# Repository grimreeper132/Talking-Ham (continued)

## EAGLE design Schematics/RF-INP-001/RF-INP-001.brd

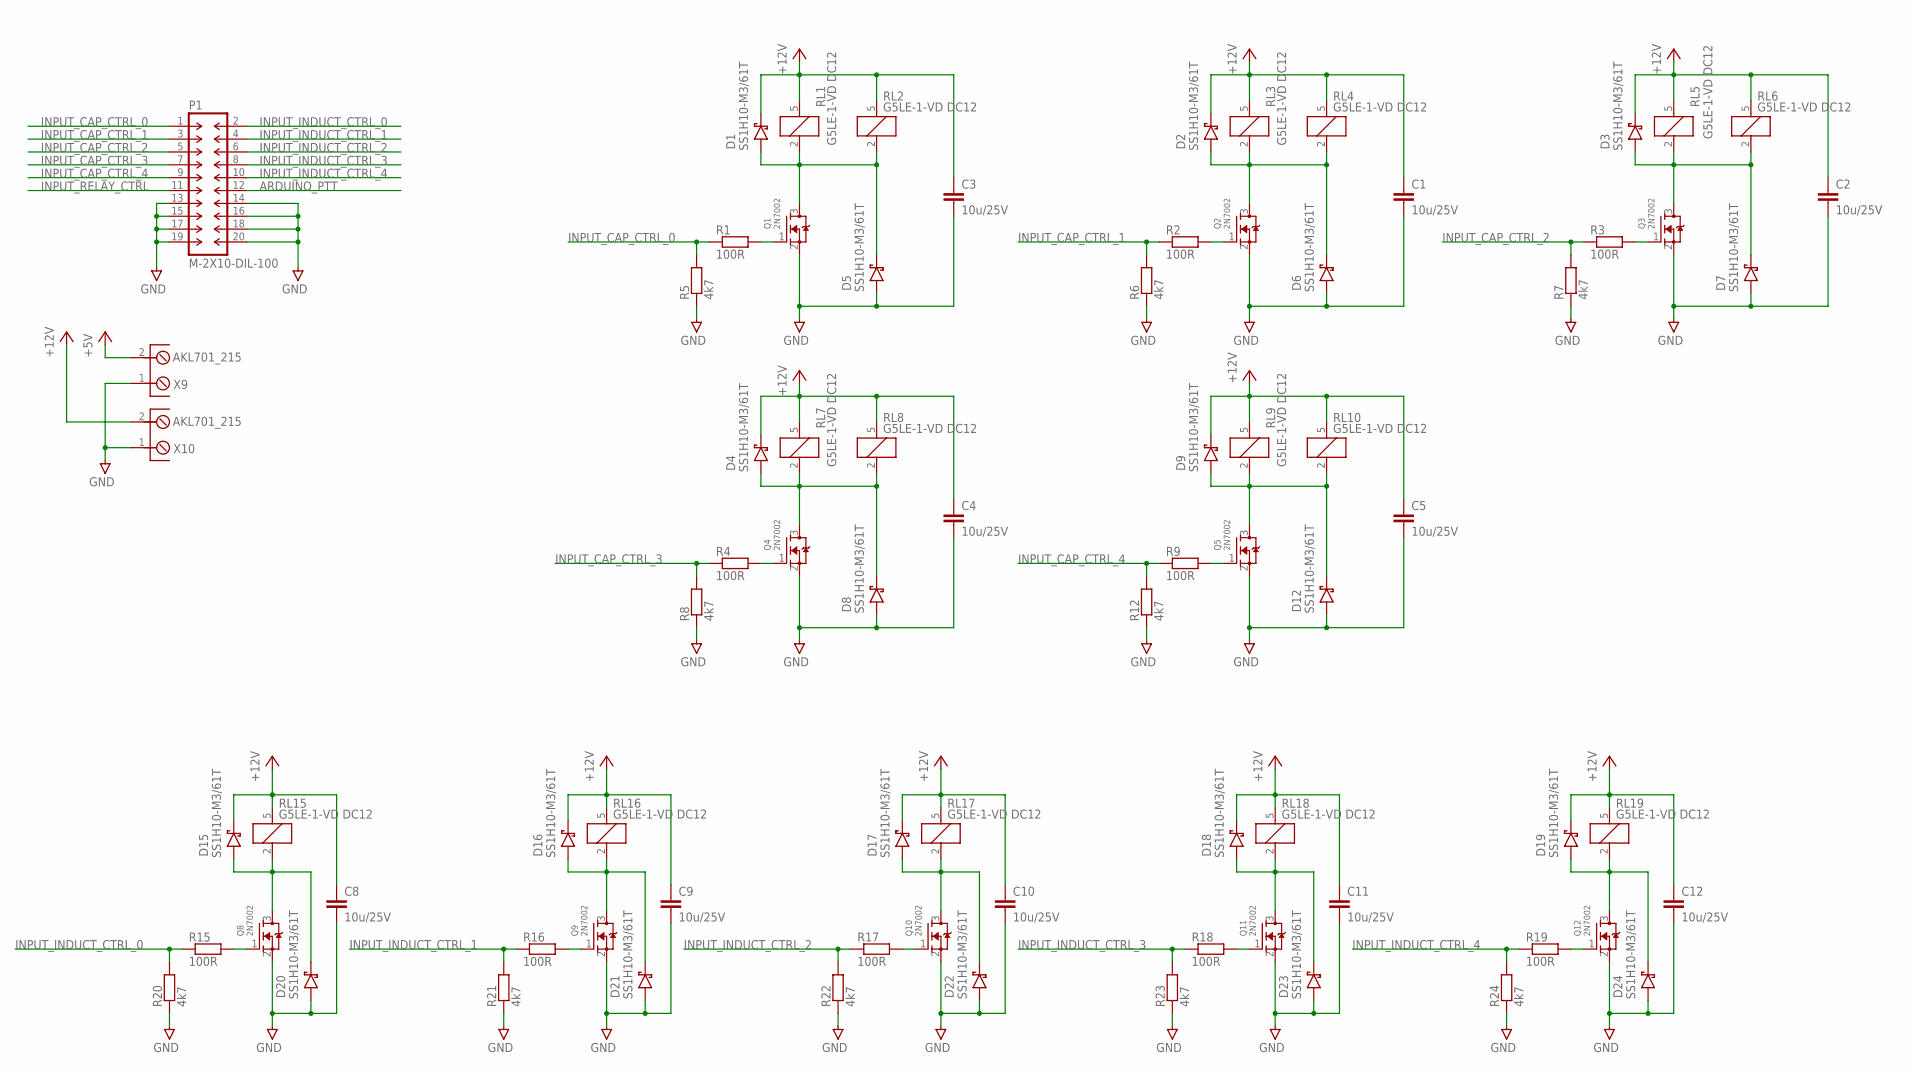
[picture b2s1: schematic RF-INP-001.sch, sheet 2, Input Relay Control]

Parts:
C1, C2, C3, C4, C5, C8, C9, C10, C11, C12: 10u/25V; C0805
D1, D2, D3, D4, D5, D6, D7, D8, D9, D12, D15, D16, D17, D18, D19, D20, D21, D22, D23, D24: SS1H10-M3/61T; SMA/DO-214AC
P1: M-2X10-DIL-100; DIL-100-2X10
Q1, Q2, Q3, Q4, Q5, Q8, Q9, Q10, Q11, Q12: 2N7002; SOT23
R1, R2, R3, R4, R9, R15, R16, R17, R18, R19: 100R; R0603
R5, R6, R7, R8, R12, R20, R21, R22, R23, R24: 4k7; R0603
RL1, RL2, RL3, RL4, RL5, RL6, RL7, RL8, RL9, RL10, RL15, RL16, RL17, RL18, RL19: G5LE-1-VD DC12; SPDT
X9, X10: AKL701_215; AKL701_2_15

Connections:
+5V: X9.2; also elsewhere on the board
+12V: C1.1, C2.1, C3.1, C4.1, C5.1, C8.1, C9.1, C10.1, C11.1, C12.1, D1.C (CATHODE), D2.C (CATHODE), D3.C (CATHODE), D4.C (CATHODE), D9.C (CATHODE), D15.C (CATHODE), D16.C (CATHODE), D17.C (CATHODE), D18.C (CATHODE), D19.C (CATHODE), RL1.5, RL2.5, RL3.5, RL4.5, RL5.5, RL6.5, RL7.5, RL8.5, RL9.5, RL10.5, RL15.5, RL16.5, RL17.5, RL18.5, RL19.5, X10.2; also elsewhere on the board
ARDUINO_PTT: P1.12; also elsewhere on the board
GND: C1.2, C2.2, C3.2, C4.2, C5.2, C8.2, C9.2, C10.2, C11.2, C12.2, D5.A (ANODE), D6.A (ANODE), D7.A (ANODE), D8.A (ANODE), D12.A (ANODE), D20.A (ANODE), D21.A (ANODE), D22.A (ANODE), D23.A (ANODE), D24.A (ANODE), P1.13, P1.14, P1.15, P1.16, P1.17, P1.18, P1.19, P1.20, Q1.2 (S), Q2.2 (S), Q3.2 (S), Q4.2 (S), Q5.2 (S), Q8.2 (S), Q9.2 (S), Q10.2 (S), Q11.2 (S), Q12.2 (S), R5.1, R6.1, R7.1, R8.1, R12.1, R20.1, R21.1, R22.1, R23.1, R24.1, X9.1, X10.1; also elsewhere on the board
INPUT_CAP_CTRL_0: P1.1, R1.1, R5.2
INPUT_CAP_CTRL_1: P1.3, R2.1, R6.2
INPUT_CAP_CTRL_2: P1.5, R3.1, R7.2
INPUT_CAP_CTRL_3: P1.7, R4.1, R8.2
INPUT_CAP_CTRL_4: P1.9, R9.1, R12.2
INPUT_INDUCT_CTRL_0: P1.2, R15.1, R20.2
INPUT_INDUCT_CTRL_1: P1.4, R16.1, R21.2
INPUT_INDUCT_CTRL_2: P1.6, R17.1, R22.2
INPUT_INDUCT_CTRL_3: P1.8, R18.1, R23.2
INPUT_INDUCT_CTRL_4: P1.10, R19.1, R24.2
INPUT_RELAY_CTRL: P1.11; also elsewhere on the board
unnamed: D16.A (ANODE), D21.C (CATHODE), Q9.3 (D), RL16.2
unnamed: Q9.1 (G), R16.2
unnamed: D17.A (ANODE), D22.C (CATHODE), Q10.3 (D), RL17.2
unnamed: Q10.1 (G), R17.2
unnamed: D18.A (ANODE), D23.C (CATHODE), Q11.3 (D), RL18.2
unnamed: Q11.1 (G), R18.2
unnamed: D19.A (ANODE), D24.C (CATHODE), Q12.3 (D), RL19.2
unnamed: Q12.1 (G), R19.2
unnamed: D1.A (ANODE), D5.C (CATHODE), Q1.3 (D), RL1.2, RL2.2
unnamed: Q1.1 (G), R1.2
unnamed: D2.A (ANODE), D6.C (CATHODE), Q2.3 (D), RL3.2, RL4.2
unnamed: Q2.1 (G), R2.2
unnamed: D4.A (ANODE), D8.C (CATHODE), Q4.3 (D), RL7.2, RL8.2
unnamed: Q4.1 (G), R4.2
unnamed: D9.A (ANODE), D12.C (CATHODE), Q5.3 (D), RL9.2, RL10.2
unnamed: Q5.1 (G), R9.2
unnamed: D3.A (ANODE), D7.C (CATHODE), Q3.3 (D), RL5.2, RL6.2
unnamed: Q3.1 (G), R3.2
unnamed: D15.A (ANODE), D20.C (CATHODE), Q8.3 (D), RL15.2
unnamed: Q8.1 (G), R15.2

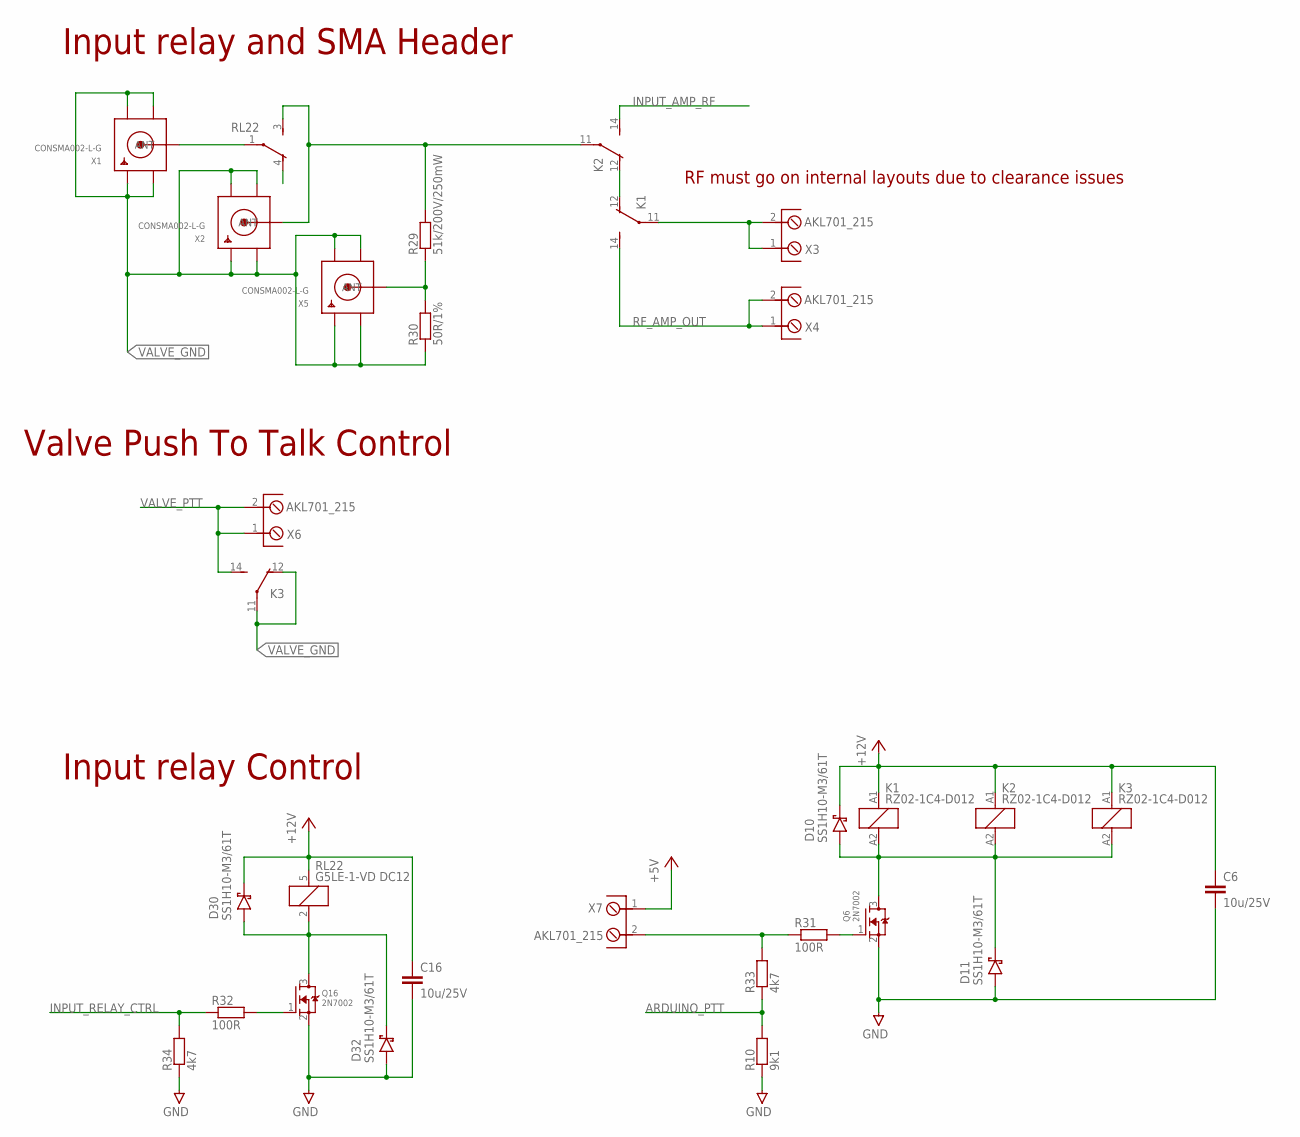
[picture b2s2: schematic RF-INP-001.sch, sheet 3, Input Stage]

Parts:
C6, C16: 10u/25V; C0805
D10, D11, D30, D32: SS1H10-M3/61T; SMA/DO-214AC
K1, K2, K3: RZ02-1C4-D012; 12A-5MM
Q6, Q16: 2N7002; SOT23
R10: 9k1; R0603
R29: 51k/200V/250mW; R2512
R30: 50R/1%; R0603
R31, R32: 100R; R0603
R33, R34: 4k7; R0603
RL22: G5LE-1-VD DC12; SPDT
X1, X2, X5: CONSMA002-L-G; SMA90_DIP
X3, X4, X6, X7: AKL701_215; AKL701_2_15

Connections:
+5V: X7.1; also elsewhere on the board
+12V: C6.1, C16.1, D10.C (CATHODE), D30.C (CATHODE), K1.A1 (1), K2.A1 (1), K3.A1 (1), RL22.5; also elsewhere on the board
ARDUINO_PTT: R10.2, R33.1; also elsewhere on the board
GND: C6.2, C16.2, D11.A (ANODE), D32.A (ANODE), Q6.2 (S), Q16.2 (S), R10.1, R34.1; also elsewhere on the board
INPUT_AMP_RF: K2.14 (NO); also elsewhere on the board
INPUT_RELAY_CTRL: R32.1, R34.2; also elsewhere on the board
unnamed: D10.A (ANODE), D11.C (CATHODE), K1.A2 (2), K2.A2 (2), K3.A2 (2), Q6.3 (D)
unnamed: K1.12 (NC), K2.12 (NC)
unnamed: K1.11 (COM), X3.1, X3.2
unnamed: Q6.1 (G), R31.2
unnamed: D30.A (ANODE), D32.C (CATHODE), Q16.3 (D), RL22.2
unnamed: Q16.1 (G), R32.2
unnamed: R29.1, R30.2, X5.ANTENNA (ANT)
unnamed: RL22.1, X1.ANTENNA (ANT)
unnamed: R31.1, R33.2, X7.2
unnamed: K2.11 (COM), R29.2, RL22.3, X2.ANTENNA (ANT)
RF_AMP_OUT: K1.14 (NO), X4.1, X4.2
VALVE_GND: K3.11 (COM), K3.12 (NC), R30.1, X1.GND1, X1.GND2, X1.GND3, X1.GND4, X2.GND1, X2.GND2, X2.GND3, X2.GND4, X5.GND1, X5.GND2, X5.GND3, X5.GND4; also elsewhere on the board
VALVE_PTT: K3.14 (NO), X6.1, X6.2

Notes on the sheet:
Input relay and SMA Header
Input relay Control
Valve Push To Talk Control
RF must go on internal layouts due to clearance issues

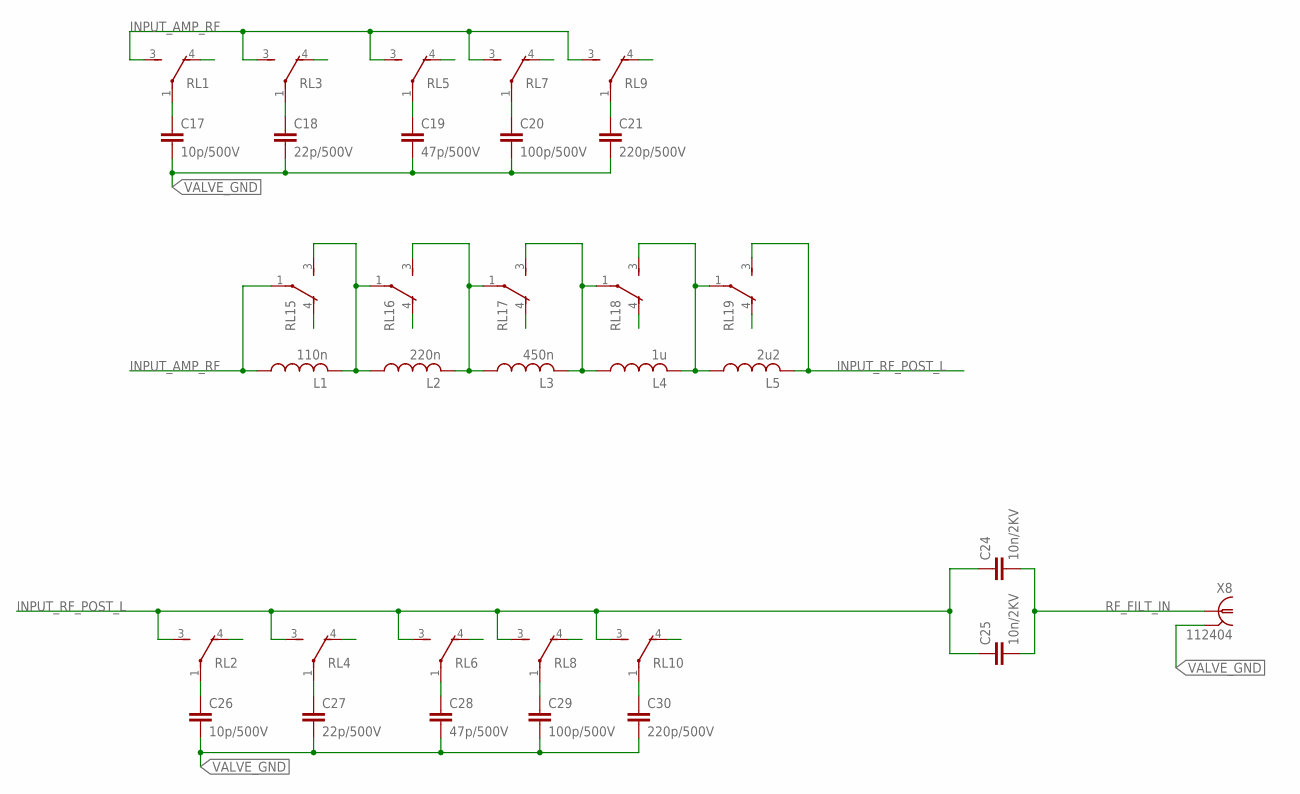
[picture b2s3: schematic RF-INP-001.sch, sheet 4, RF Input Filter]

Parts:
C17, C26: 10p/500V; C1812
C18, C27: 22p/500V; C1812
C19, C28: 47p/500V; C1812
C20, C29: 100p/500V; C1812
C21, C30: 220p/500V; C1812
C24, C25: 10n/2KV; C1812
L1: 110n; T80-6
L2: 220n; T80-6
L3: 450n; T80-6
L4: 1u; T80-6
L5: 2u2; T80-6
RL1, RL2, RL3, RL4, RL5, RL6, RL7, RL8, RL9, RL10, RL15, RL16, RL17, RL18, RL19: G5LE-1-VD DC12; SPDT
X8: 112404

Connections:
INPUT_AMP_RF: L1.1, RL1.3, RL3.3, RL5.3, RL7.3, RL9.3, RL15.1; also elsewhere on the board
INPUT_RF_POST_L: C24.1, C25.1, L5.2, RL2.3, RL4.3, RL6.3, RL8.3, RL10.3, RL19.3
unnamed: C17.1, RL1.1
unnamed: C26.1, RL2.1
unnamed: C27.1, RL4.1
unnamed: C28.1, RL6.1
unnamed: C29.1, RL8.1
unnamed: C30.1, RL10.1
unnamed: C18.1, RL3.1
unnamed: C19.1, RL5.1
unnamed: C21.1, RL9.1
unnamed: C20.1, RL7.1
unnamed: L4.2, L5.1, RL18.3, RL19.1
unnamed: L3.2, L4.1, RL17.3, RL18.1
unnamed: L2.2, L3.1, RL16.3, RL17.1
unnamed: L1.2, L2.1, RL15.3, RL16.1
RF_FILT_IN: C24.2, C25.2, X8.1
VALVE_GND: C17.2, C18.2, C19.2, C20.2, C21.2, C26.2, C27.2, C28.2, C29.2, C30.2, X8.2, X8.3 (2), X8.4 (2), X8.5 (2); also elsewhere on the board

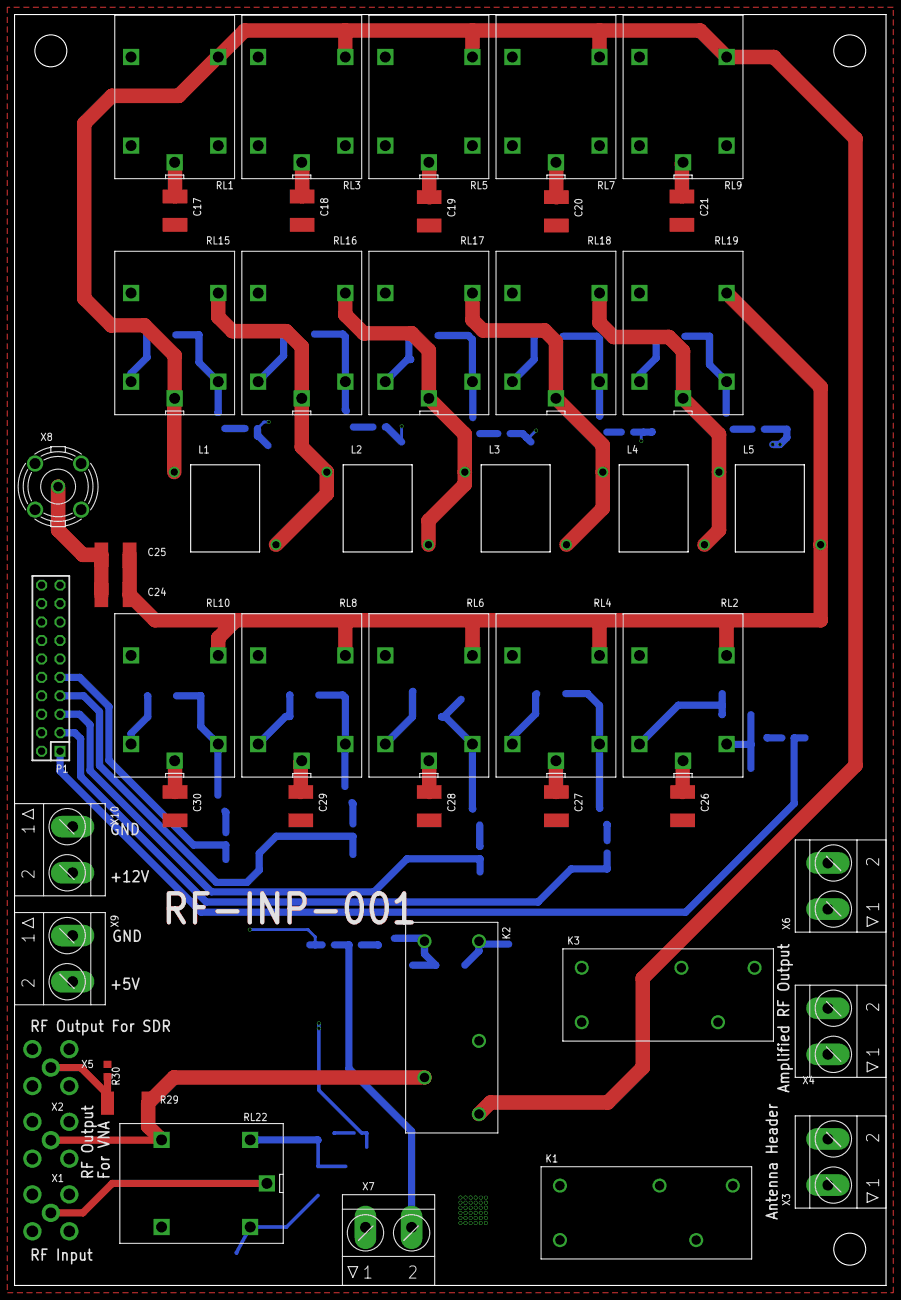
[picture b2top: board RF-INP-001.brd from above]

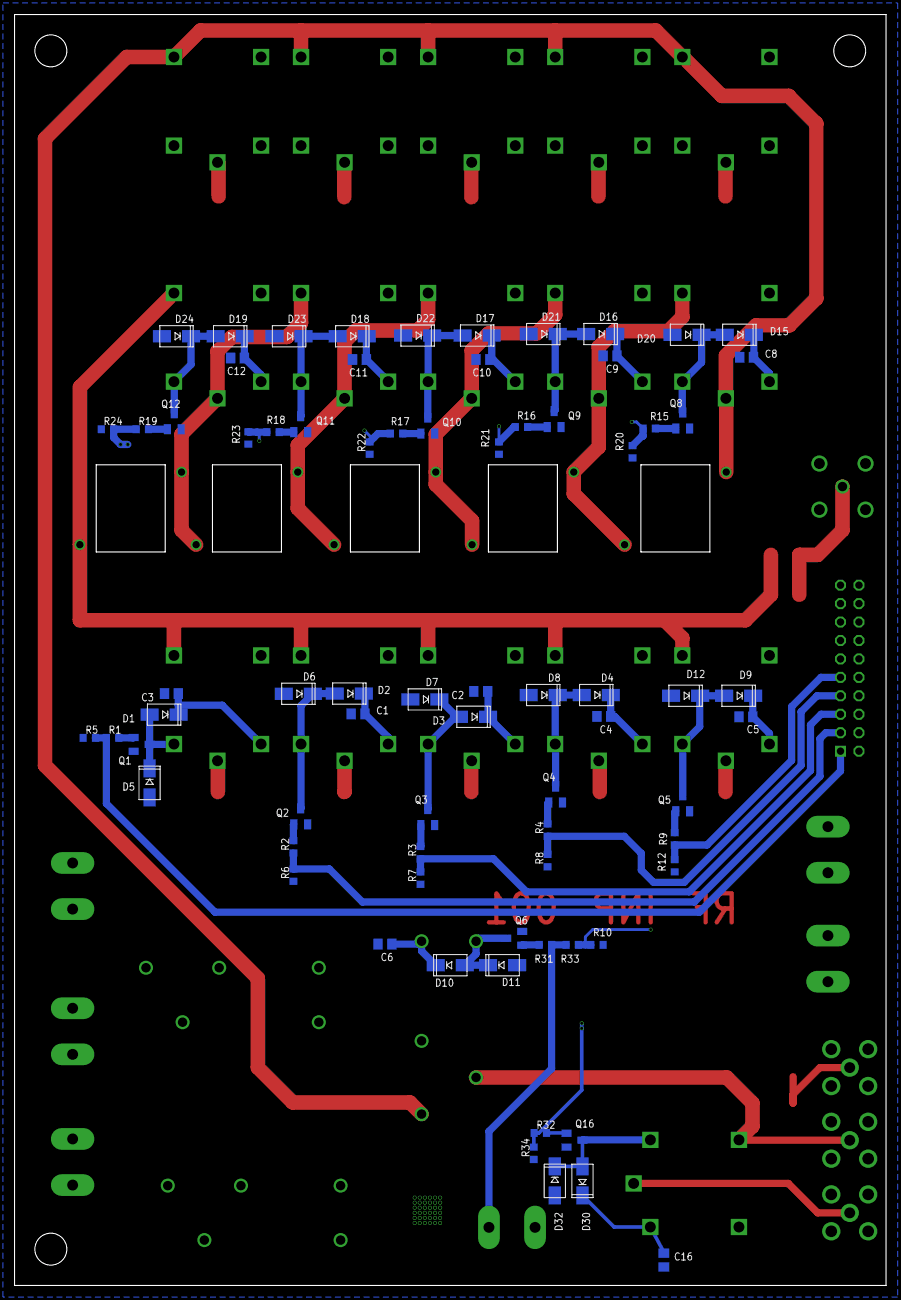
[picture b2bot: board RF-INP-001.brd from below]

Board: 4 copper layers, 120.0 x 175.0 mm, 122 parts (73 on the bottom side), 65 nets.

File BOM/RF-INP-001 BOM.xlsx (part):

|  |  | Board ID |  |  | Engineer |  |  | Project |  |  | Job NO.
 |  |  | Revision | 1 |  | Approval |  |  | Customer |  |  | Boards Required | 1
 | (don't touch)
 | Component Number | Type Colour | Schematic Ref | Quantity | Spare Parts | Description | Footprint | Value | Tolerance | Manufacturer | Manufacturer Part Number | Preferred Supplier | Order-code | Alternate Supplier | Alt Order-Code | Unit/Reel Price | Packaging | Reel QTY | Stock | Price per board | Total Price (all boards) | Order Quantity | Order Price
 | 0 | 1 | C1, C2, C3, C4, C5, C6, C8, C9, C10, C11, C12, C16 | 12 |  | X5R Ceramic Capacitor | C0805 | 10u/25V |  | Samsung Electro-Mechanics | CL21A106KAYNNNE | Mouser | 187-CL21A106KAYNNNE |  |  | 0.13700000000000001 | Cut Tape | 1000 |  | 1.6440000000000001 | 1.6440000000000001 | 12 | 1.6440000000000001
 | 1 | 2 | R1, R2, R3, R4, R9, R15, R16, R17, R18, R19, R31, R32 | 12 |  | Thick Film Resistor | R0603 | 100R | 0.01 | Vishay/Dale | CRCW0603100RFKEAC | Mouser | 71-CRCW0603100RFKEAC |  |  | 7.6999999999999999E-2 | Cut Tape | 1000 |  | 0.92399999999999993 | 0.92399999999999993 | 12 | 0.92399999999999993
 | 2 | 2 | R29 | 1 |  | Thick Film Resistor | R2512 | 51k/200V/250mW | 0.05 | Yageo | RC2512JK-0751KL | Mouser | 603-RC2512JK-0751KL |  |  | 0.27500000000000002 | Cut Tape | 1000 |  | 0.27500000000000002 | 0.27500000000000002 | 1 | 0.27500000000000002
 | 3 | 2 | R30 | 1 |  | Thick Film Resistor | R0603 | 50R | 0.01 | Vishay / Dale | CRCW060350R0FKTA | Mouser | 71-CRCW0603-50 |  |  | 0.17599999999999999 | Cut Tape | 1000 |  | 0.17599999999999999 | 0.17599999999999999 | 1 | 0.17599999999999999
 | 4 | 2 | R5, R6, R7, R8, R10, R12, R20, R21, R22, R23, R24, R34 | 12 |  | Thick Film Resistor | R0603 | 4k7 | 0.05 | Vishay / Dale | CRCW06034K70JNEAC | Mouser | 71-CRCW06034K70JNEAC |  |  | 7.6999999999999999E-2 | Cut Tape | 1000 |  | 0.92399999999999993 | 0.92399999999999993 | 12 | 0.92399999999999993
 | 5 | 2 | R33 | 1 |  | Thick Film Resistor | R0603 | 9k1 | 0.05 | ROHM Semiconductor | SDR03EZPJ912 | Mouser | 755-SDR03EZPJ912 |  |  | 7.6999999999999999E-2 | Cut Tape | 1000 |  | 7.6999999999999999E-2 | 7.6999999999999999E-2 | 1 | 7.6999999999999999E-2
 | 6 | 3 | L1 | 1 |  | RF Inductor Toroid Core | T80-6 | 5 turns 20 AWG |  | Micrometals | T60-6 | Pace Components | link |  |  | 0.88 | Cut Tape | 1000 |  | 0.88 | 0.88 | 1 | 0.88
 | 7 | 3 | L2 | 1 |  | RF Inductor Toroid Core | T80-6 | 7 turns 20 AWG |  | Micrometals | T60-6 | Pace Components | link |  |  | 0.88 | Cut Tape | 1000 |  | 0.88 | 0.88 | 1 | 0.88
 | 8 | 3 | L3 | 1 |  | RF Inductor Toroid Core | T80-6 | 10 turns 20 AWG |  | Micrometals | T60-6 | Pace Components | link |  |  | 0.88 | Cut Tape | 1000 |  | 0.88 | 0.88 | 1 | 0.88
 | 9 | 3 | L4 | 1 |  | RF Inductor Toroid Core | T80-6 | 15 turns 20 AWG |  | Micrometals | T60-6 | Pace Components | link |  |  | 0.88 | Cut Tape | 1000 |  | 0.88 | 0.88 | 1 | 0.88
 | 10 | 3 | L5 | 1 |  | RF Inductor Toroid Core | T80-6 | 22 turns 20 AWG |  | Micrometals | T60-6 | Pace Components | link |  |  | 0.88 | Cut Tape | 1000 |  | 0.88 | 0.88 | 1 | 0.88
 | 11 | 4 | D1, D2, D3, D4, D5, D6, D7, D8, D9, D10, D11, D12, D15, D16, D17, D18, D19, D20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 | 24 |  | Schottky Diode | SMA | 0.62V 1A |  | Vishay General Semiconductor | SS1H10-M3/61T | Mouser | 78-SS1H10-M361T |  |  | 0.28199999999999997 | Cut Tape | 1000 |  | 6.7679999999999989 | 6.7679999999999989 | 24 | 6.7679999999999989
 | 12 | 6 | Q1, Q2, Q3, Q4, Q5, Q6, Q8, Q9, Q10, Q11, Q12, Q16 | 12 |  | N-Channel MOSFET | SOT23 |  |  | Nexperia | 2N7002NXAKR | Mouser | 771-2N7002NXAKR |  |  | 7.6999999999999999E-2 | Cut Tape | 1000 |  | 0.92399999999999993 | 0.92399999999999993 | 12 | 0.92399999999999993
 | 13 | 7 | K1, K2, K3 | 3 |  | General Purpose Relay | Custom |  |  | TE Connectivity / P&B | 3-1415899-5 | Mouser | 655-3-1415899-5 |  |  | 1.5 | Cut Tape | 1000 |  | 4.5 | 4.5 | 3 | 4.5
 | 14 | 7 | P1 | 1 |  | 20 pin Headeer | 2.54mm 2 by 10 pos | 20 pins |  | Amphenol FCI | 10129381-920001BLF | Mouser | 649-1012938192001BLF |  |  | 0.32800000000000001 | Cut Tape | 1000 |  | 0.32800000000000001 | 0.32800000000000001 | 1 | 0.32800000000000001
 | 15 | 7 | RL1, RL2, RL3, RL4, RL5, RL6, RL7, RL8, RL9, RL10, RL15, RL16, RL17, RL18, RL19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 | 16 |  | General Purpose Relay | G5LE | SPDT |  | Omron Electronics | G5LE-1-VD DC12 | Mouser | 653-G5LE-1-VDDC12 |  |  | 1.07 | Cut Tape | 1000 |  | 17.12 | 17.12 | 16 | 17.12
 | 16 | 8 | X1, X2, X5 | 3 |  | SMA Connector | Through hole SMA |  |  | Linx Technologies | CONSMA002-L-G | Mouser | 712-CONSMA002-L-G | Digi-Key | CONSMA002-L-G-ND | 3.11 | Cut Tape | 1000 |  | 9.33 | 9.33 | 3 | 9.33
 | 17 | 8 | X3, X4, X6, X7, X9, X10 | 6 |  | Terminal Block | 6.35mm 2 pos | 2 pos |  | Phoenix Contact | 1714955 | Mouser | 651-1714955 | Digi-Key | 277-1269-ND | 0.96299999999999997 | Cut Tape | 1000 |  | 5.7779999999999996 | 5.7779999999999996 | 6 | 5.7779999999999996
 | 18 | 8 | X8 | 1 |  | BNC RF Connector | TH BNC |  |  | Amphenol RF | 112404 | Mouser | 523-112404 |  |  | 2.1800000000000002 | Cut Tape | 1000 |  | 2.1800000000000002 | 2.1800000000000002 | 1 | 2.1800000000000002
 | 19 |  |  |  |  |  |  |  |  |  |  |  |  |  |  |  | Cut Tape | 1000 |  | 0 | 0 | 0 | 0
 | 20 |  |  |  |  |  |  |  |  |  |  |  |  |  |  |  | Cut Tape | 1000 |  | 0 | 0 | 0 | 0
 | 21 |  |  |  |  |  |  |  |  |  |  |  |  |  |  |  | Cut Tape | 1000 |  | 0 | 0 | 0 | 0
 | 22 |  |  |  |  |  |  |  |  |  |  |  |  |  |  |  | Cut Tape | 1000 |  | 0 | 0 | 0 | 0
 | 23 |  |  |  |  |  |  |  |  |  |  |  |  |  |  |  | Cut Tape | 1000 |  | 0 | 0 | 0 | 0
 | 24 |  |  |  |  |  |  |  |  |  |  |  |  |  |  |  | Cut Tape | 1000 |  | 0 | 0 | 0 | 0
 | 25 |  |  |  |  |  |  |  |  |  |  |  |  |  |  |  | Cut Tape | 1000 |  | 0 | 0 | 0 | 0
 | 26 |  |  |  |  |  |  |  |  |  |  |  |  |  |  |  | Cut Tape | 1000 |  | 0 | 0 | 0 | 0
 | 27 |  |  |  |  |  |  |  |  |  |  |  |  |  |  |  | Cut Tape | 1000 |  | 0 | 0 | 0 | 0
 | 28 |  |  |  |  |  |  |  |  |  |  |  |  |  |  |  | Cut Tape | 1000 |  | 0 | 0 | 0 | 0
 | 29 |  |  |  |  |  |  |  |  |  |  |  |  |  |  |  | Cut Tape | 1000 |  | 0 | 0 | 0 | 0
 | 30 |  |  |  |  |  |  |  |  |  |  |  |  |  |  |  | Cut Tape | 1000 |  | 0 | 0 | 0 | 0
 | 31 |  |  |  |  |  |  |  |  |  |  |  |  |  |  |  | Cut Tape | 1000 |  | 0 | 0 | 0 | 0
 | 32 |  |  |  |  |  |  |  |  |  |  |  |  |  |  |  | Cut Tape | 1000 |  | 0 | 0 | 0 | 0
 | 33 |  |  |  |  |  |  |  |  |  |  |  |  |  |  |  | Cut Tape | 1000 |  | 0 | 0 | 0 | 0
 | 34 |  |  |  |  |  |  |  |  |  |  |  |  |  |  |  | Cut Tape | 1000 |  | 0 | 0 | 0 | 0
 | 35 |  |  |  |  |  |  |  |  |  |  |  |  |  |  |  | Cut Tape | 1000 |  | 0 | 0 | 0 | 0
 | 36 |  |  |  |  |  |  |  |  |  |  |  |  |  |  |  | Cut Tape | 1000 |  | 0 | 0 | 0 | 0
 | 37 |  |  |  |  |  |  |  |  |  |  |  |  |  |  |  | Cut Tape | 1000 |  | 0 | 0 | 0 | 0
 | 38 |  |  |  |  |  |  |  |  |  |  |  |  |  |  |  | Cut Tape | 1000 |  | 0 | 0 | 0 | 0
 | 39 |  |  |  |  |  |  |  |  |  |  |  |  |  |  |  | Cut Tape | 1000 |  | 0 | 0 | 0 | 0
 | 40 |  |  |  |  |  |  |  |  |  |  |  |  |  |  |  | Cut Tape | 1000 |  | 0 | 0 | 0 | 0
 | 41 |  |  |  |  |  |  |  |  |  |  |  |  |  |  |  | Cut Tape | 1000 |  | 0 | 0 | 0 | 0
 | 42 |  |  |  |  |  |  |  |  |  |  |  |  |  |  |  | Cut Tape | 1000 |  | 0 | 0 | 0 | 0
 | 43 |  |  |  |  |  |  |  |  |  |  |  |  |  |  |  | Cut Tape | 1000 |  | 0 | 0 | 0 | 0
 | 44 |  |  |  |  |  |  |  |  |  |  |  |  |  |  |  | Cut Tape | 1000 |  | 0 | 0 | 0 | 0
 | 45 |  |  |  |  |  |  |  |  |  |  |  |  |  |  |  | Cut Tape | 1000 |  | 0 | 0 | 0 | 0
 | 46 |  |  |  |  |  |  |  |  |  |  |  |  |  |  |  | Cut Tape | 1000 |  | 0 | 0 | 0 | 0
 | 47 |  |  |  |  |  |  |  |  |  |  |  |  |  |  |  | Cut Tape | 1000 |  | 0 | 0 | 0 | 0
 | 48 |  |  |  |  |  |  |  |  |  |  |  |  |  |  |  | Cut Tape | 1000 |  | 0 | 0 | 0 | 0
 | 49 |  |  |  |  |  |  |  |  |  |  |  |  |  |  |  | Cut Tape | 1000 |  | 0 | 0 | 0 | 0
 | 50 |  |  |  |  |  |  |  |  |  |  |  |  |  |  |  | Cut Tape | 1000 |  | 0 | 0 | 0 | 0
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
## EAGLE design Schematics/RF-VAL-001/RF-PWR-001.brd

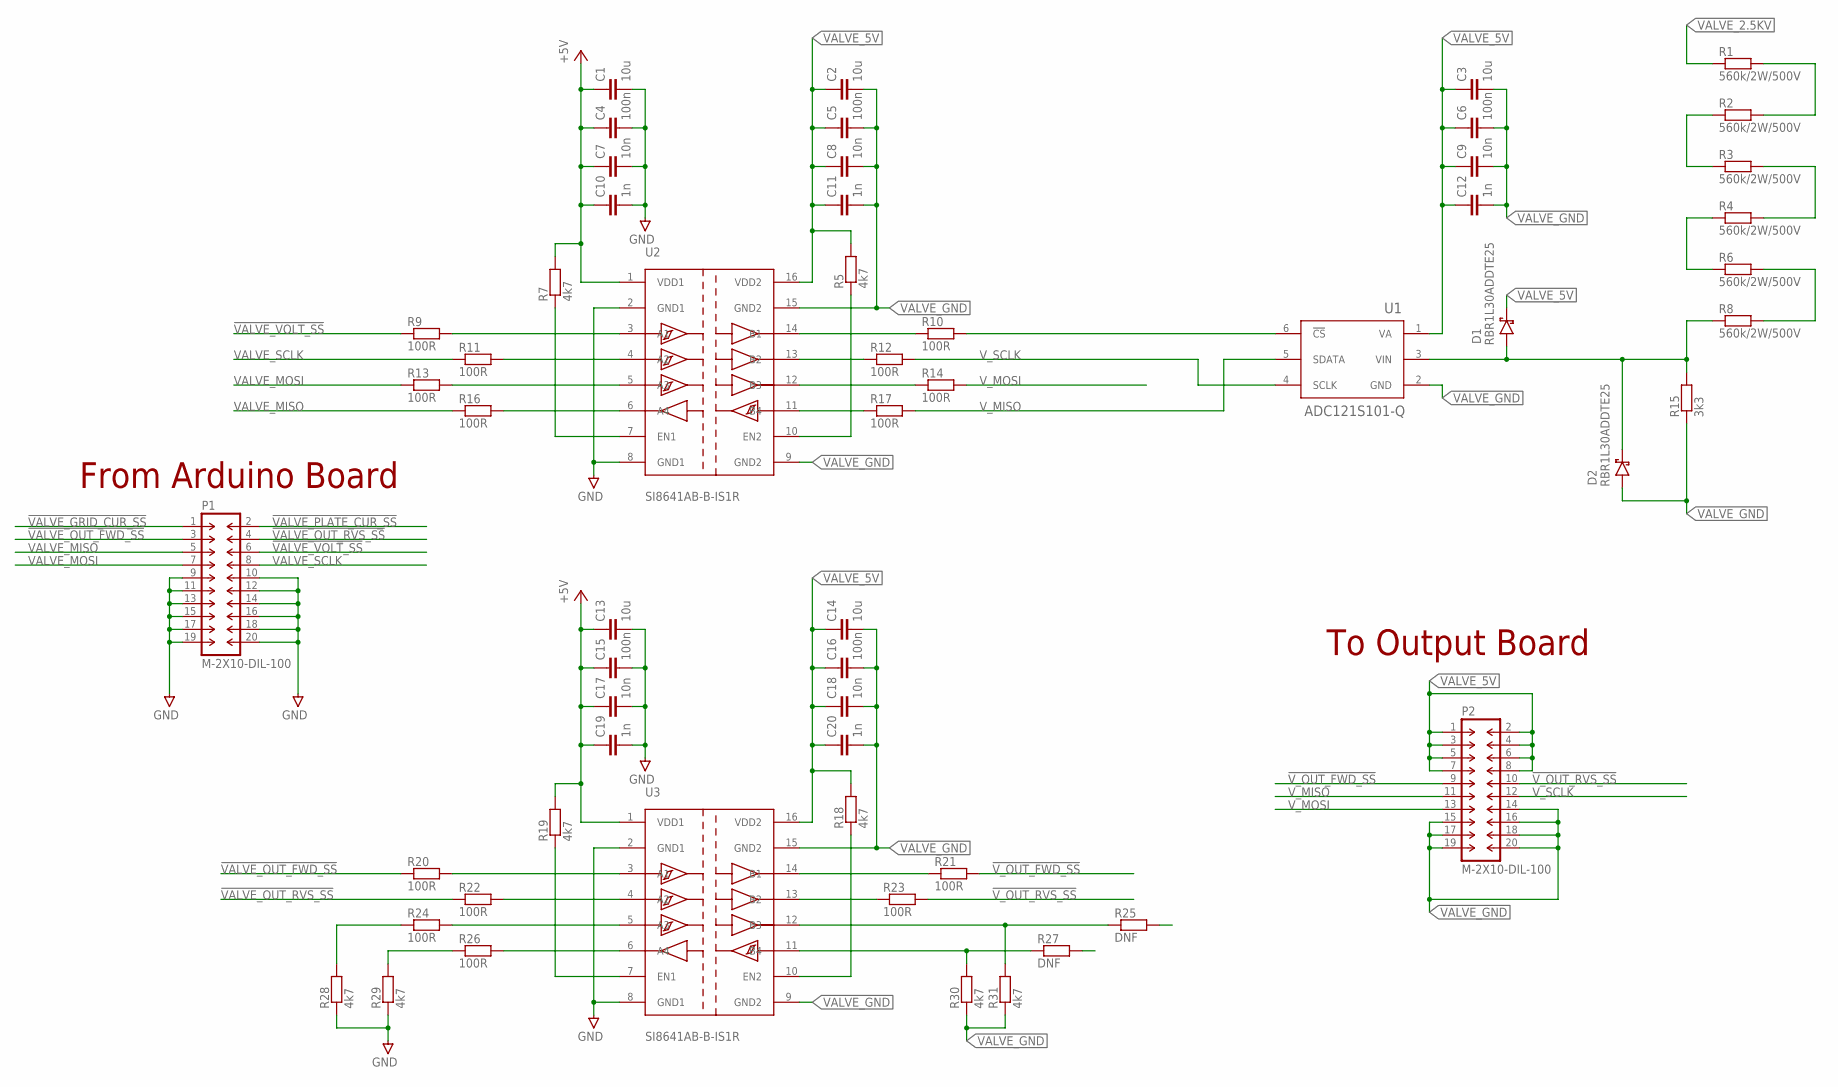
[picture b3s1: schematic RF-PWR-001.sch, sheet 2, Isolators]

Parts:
C1, C2, C3, C13, C14: 10u; C0805
C4, C5, C6, C15, C16: 100n; C0603
C7, C8, C9, C17, C18: 10n; C0603
C10, C11, C12, C19, C20: 1n; C0603
D1, D2: RBR1L30ADDTE25; SMA/DO-214AC
P1, P2: M-2X10-DIL-100; DIL-100-2X10
R1, R2, R3, R4, R6, R8: 560k/2W/500V; SMV1/SMF2
R5, R7, R18, R19, R28, R29, R30, R31: 4k7; R0603
R9, R10, R11, R12, R13, R14, R16, R17, R20, R21, R22, R23, R24, R26: 100R; R0603
R15: 3k3; R0603
R25, R27: DNF; R0603
U1: ADC121S101-Q; SOT23-6
U2, U3: SI8641AB-B-IS1R; SO16

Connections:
!VALVE_GRID_CUR_SS: P1.1; also elsewhere on the board
!VALVE_OUT_FWD_SS: P1.3, R20.1
!VALVE_OUT_RVS_SS: P1.4, R22.1
!VALVE_PLATE_CUR_SS: P1.2; also elsewhere on the board
!VALVE_VOLT_SS: P1.6, R9.1
!V_OUT_FWD_SS: P2.9, R21.2
!V_OUT_RVS_SS: P2.10, R23.2
+5V: C1.1, C4.1, C7.1, C10.1, C13.1, C15.1, C17.1, C19.1, R7.2, R19.2, U2.1 (VDD1), U3.1 (VDD1); also elsewhere on the board
GND: C1.2, C4.2, C7.2, C10.2, C13.2, C15.2, C17.2, C19.2, P1.9, P1.10, P1.11, P1.12, P1.13, P1.14, P1.15, P1.16, P1.17, P1.18, P1.19, P1.20, R28.1, R29.1, U2.2 (GND1), U2.8 (GND1), U3.2 (GND1), U3.8 (GND1); also elsewhere on the board
unnamed: R24.1, R28.2
unnamed: R13.2, U2.5 (A3)
unnamed: R16.2, U2.6 (A4)
unnamed: R11.2, U2.4 (A2)
unnamed: R9.2, U2.3 (A1)
unnamed: R7.1, U2.7 (EN1)
unnamed: R5.1, U2.10 (EN2)
unnamed: R14.1, U2.12 (B3)
unnamed: R17.1, U2.11 (B4)
unnamed: R27.1, R30.2, U3.11 (B4)
unnamed: R12.1, U2.13 (B2)
unnamed: R10.1, U2.14 (B1)
unnamed: R10.2, U1.6 (!CS)
unnamed: R23.1, U3.13 (B2)
unnamed: R21.1, U3.14 (B1)
unnamed: D1.A (ANODE), D2.C (CATHODE), R8.1, R15.2, U1.3 (VIN)
unnamed: R4.1, R6.1
unnamed: R6.2, R8.2
unnamed: R3.2, R4.2
unnamed: R1.2, R2.2
unnamed: R2.1, R3.1
unnamed: R24.2, U3.5 (A3)
unnamed: R26.2, U3.6 (A4)
unnamed: R22.2, U3.4 (A2)
unnamed: R20.2, U3.3 (A1)
unnamed: R19.1, U3.7 (EN1)
unnamed: R18.1, U3.10 (EN2)
unnamed: R25.1, R31.2, U3.12 (B3)
unnamed: R26.1, R29.2
VALVE_2.5KV: R1.1; also elsewhere on the board
VALVE_5V: C2.1, C3.1, C5.1, C6.1, C8.1, C9.1, C11.1, C12.1, C14.1, C16.1, C18.1, C20.1, D1.C (CATHODE), P2.1, P2.2, P2.3, P2.4, P2.5, P2.6, P2.7, P2.8, R5.2, R18.2, U1.1 (VA), U2.16 (VDD2), U3.16 (VDD2); also elsewhere on the board
VALVE_GND: C2.2, C3.2, C5.2, C6.2, C8.2, C9.2, C11.2, C12.2, C14.2, C16.2, C18.2, C20.2, D2.A (ANODE), P2.14, P2.15, P2.16, P2.17, P2.18, P2.19, P2.20, R15.1, R30.1, R31.1, U1.2 (GND), U2.9 (GND2), U2.15 (GND2), U3.9 (GND2), U3.15 (GND2); also elsewhere on the board
VALVE_MISO: P1.5, R16.1; also elsewhere on the board
VALVE_MOSI: P1.7, R13.1
VALVE_SCLK: P1.8, R11.1; also elsewhere on the board
V_MISO: P2.11, R17.2, U1.5 (SDATA)
V_MOSI: P2.13, R14.2
V_SCLK: P2.12, R12.2, U1.4 (SCLK)

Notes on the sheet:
To Output Board
From Arduino Board

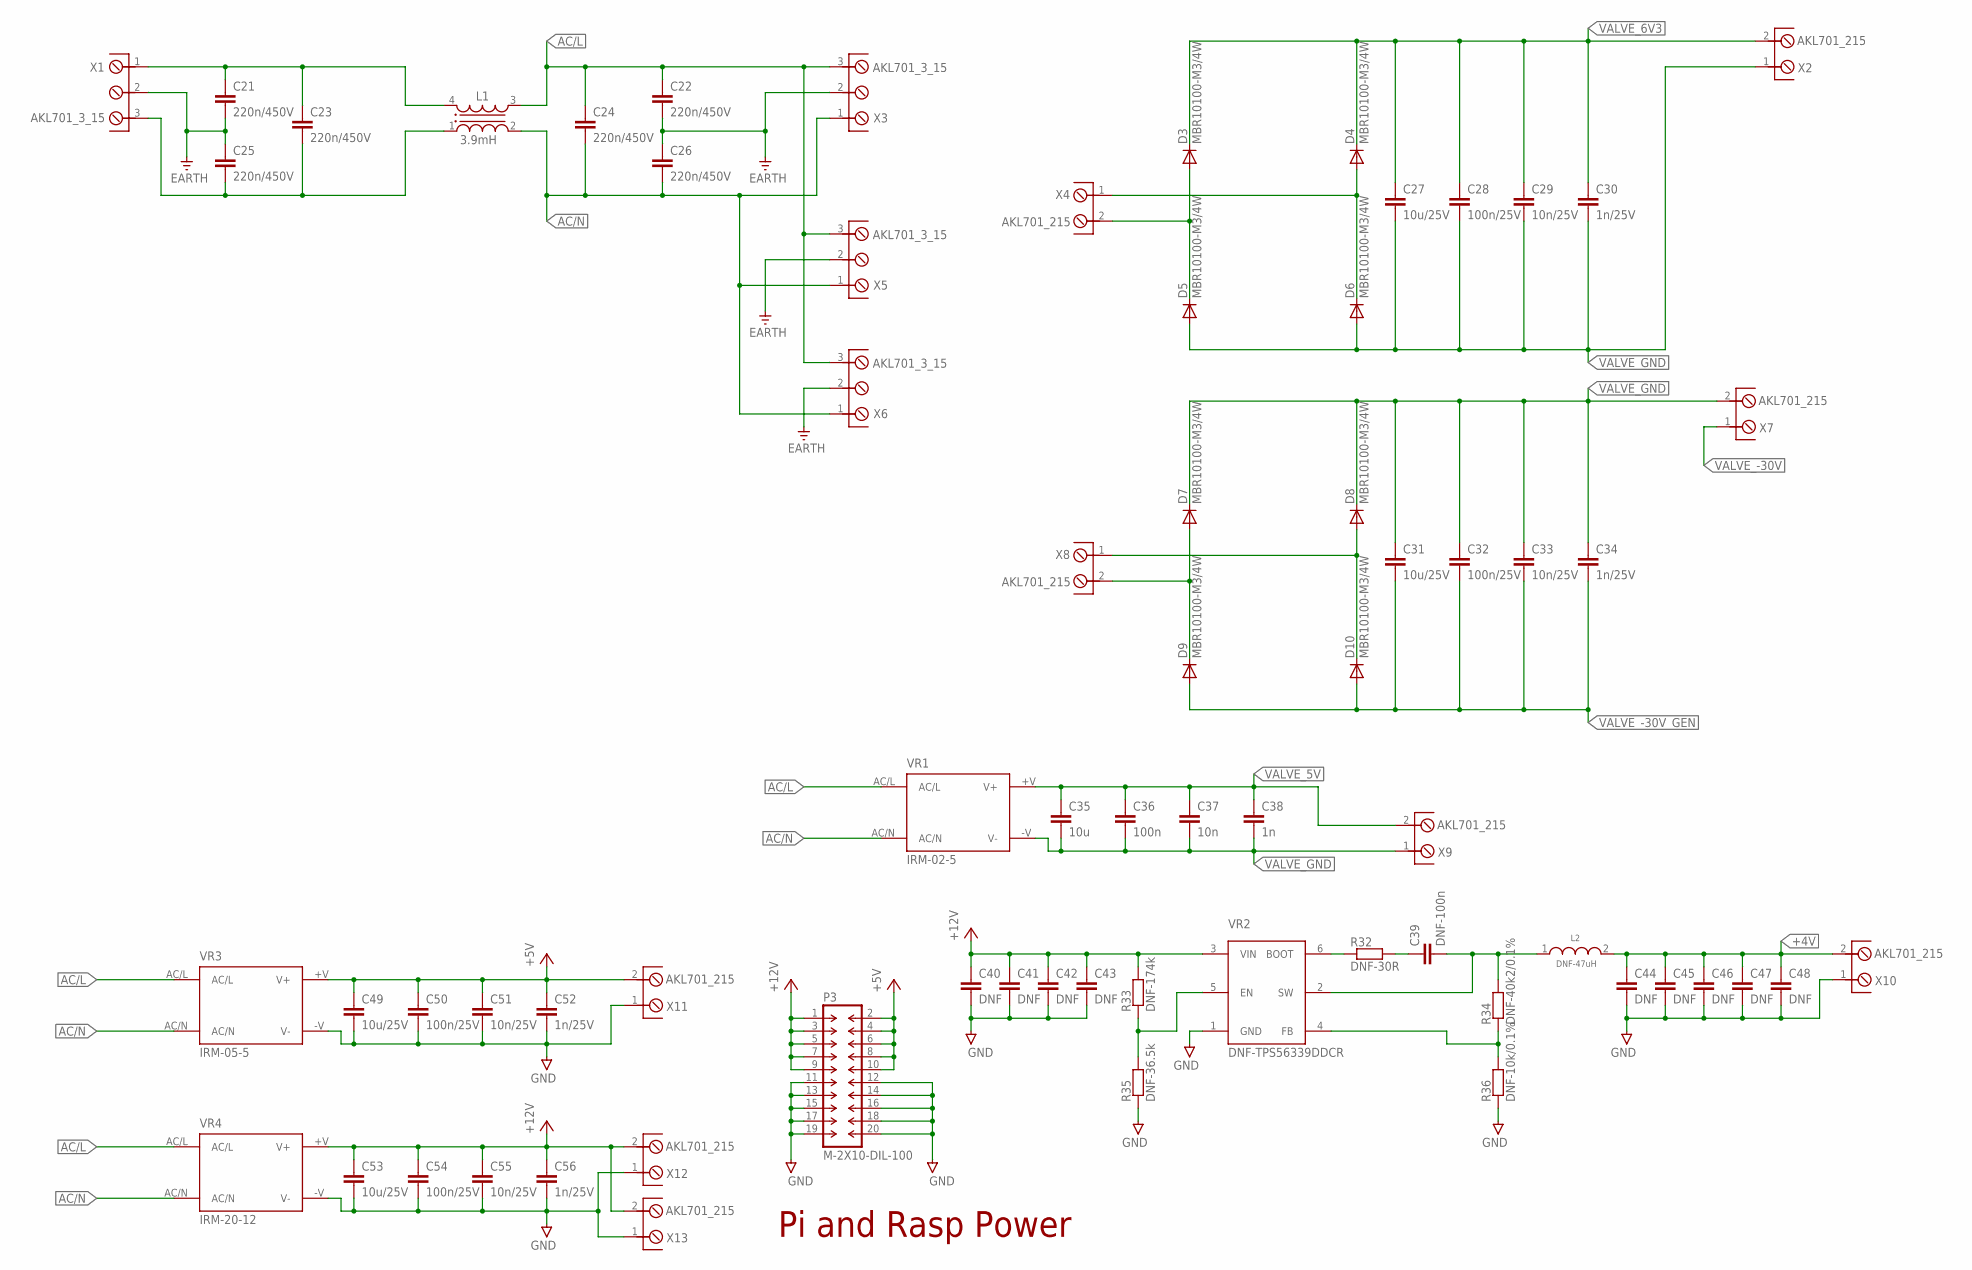
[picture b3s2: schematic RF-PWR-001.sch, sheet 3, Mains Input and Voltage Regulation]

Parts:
C21, C22, C23, C24, C25, C26: 220n/450V; C1210
C27, C31, C49, C53: 10u/25V; C0805
C28, C32, C50, C54: 100n/25V; C0603
C29, C33, C51, C55: 10n/25V; C0603
C30, C34, C52, C56: 1n/25V; C0603
C35: 10u; C0805
C36: 100n; C0603
C37: 10n; C0603
C38: 1n; C0603
C39: DNF-100n; C0603
C40, C45: DNF; C0805
C41, C42, C43, C46, C47, C48: DNF; C0603
C44: DNF; C1206
D3, D4, D5, D6, D7, D8, D9, D10: MBR10100-M3/4W; TO220ACS
L1: 3.9mH; WE-FCL_ET35
L2: DNF-47uH; WE-HCF_2920_ROUND
P3: M-2X10-DIL-100; DIL-100-2X10
R32: DNF-30R; R0603
R33: DNF-174k; R0603
R34: DNF-40k2/0.1%; R0603
R35: DNF-36.5k; R0603
R36: DNF-10k/0.1%; R0603
VR1: IRM-02-5; IRM_1-2_TH
VR2: DNF-TPS56339DDCR; SOT23-6
VR3: IRM-05-5; IRM_5-10_TH
VR4: IRM-20-12; IRM_15-20_TH
X1, X3, X5, X6: AKL701_3_15
X2, X4, X7, X8, X9, X10, X11, X12, X13: AKL701_215; AKL701_2_15

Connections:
+4V: C44.1, C45.1, C46.1, C47.1, C48.1, L2.2, X10.2
+5V: C49.1, C50.1, C51.1, C52.1, P3.2, P3.4, P3.6, P3.8, P3.10, VR3.+V (V+), X11.2; also elsewhere on the board
+12V: C40.1, C41.1, C42.1, C43.1, C53.1, C54.1, C55.1, C56.1, P3.1, P3.3, P3.5, P3.7, P3.9, R33.2, VR2.3 (VIN), VR4.+V (V+), X12.2, X13.2
AC/L: C22.1, C24.1, L1.3 (2), VR1.AC/L, VR3.AC/L, VR4.AC/L, X3.3, X5.3, X6.3
AC/N: C24.2, C26.2, L1.2 (3), VR1.AC/N, VR3.AC/N, VR4.AC/N, X3.1, X5.1, X6.1
EARTH: C21.2, C22.2, C25.1, C26.1, X1.2, X3.2, X5.2, X6.2
GND: C40.2, C41.2, C42.2, C43.2, C44.2, C45.2, C46.2, C47.2, C48.2, C49.2, C50.2, C51.2, C52.2, C53.2, C54.2, C55.2, C56.2, P3.11, P3.12, P3.13, P3.14, P3.15, P3.16, P3.17, P3.18, P3.19, P3.20, R35.1, R36.1, VR2.1 (GND), VR3.-V (V-), VR4.-V (V-), X10.1, X11.1, X12.1, X13.1; also elsewhere on the board
unnamed: D3.A, D5.C, X4.2
unnamed: D4.A, D6.C, X4.1
unnamed: R33.1, R35.2, VR2.5 (EN)
unnamed: D7.A, D9.C, X8.2
unnamed: D8.A, D10.C, X8.1
unnamed: C21.1, C23.1, L1.4 (1), X1.1
unnamed: C23.2, C25.2, L1.1 (4), X1.3
unnamed: C39.1, R32.2
unnamed: C39.2, L2.1, R34.2, VR2.2 (SW)
unnamed: R34.1, R36.2, VR2.4 (FB)
unnamed: R32.1, VR2.6 (BOOT)
VALVE_5V: C35.1, C36.1, C37.1, C38.1, VR1.+V (V+), X9.2; also elsewhere on the board
VALVE_6V3: C27.1, C28.1, C29.1, C30.1, D3.C, D4.C, X2.2
VALVE_-30V: X7.1; also elsewhere on the board
VALVE_-30V_GEN: C31.2, C32.2, C33.2, C34.2, D9.A, D10.A; also elsewhere on the board
VALVE_GND: C27.2, C28.2, C29.2, C30.2, C31.1, C32.1, C33.1, C34.1, C35.2, C36.2, C37.2, C38.2, D5.A, D6.A, D7.C, D8.C, VR1.-V (V-), X2.1, X7.2, X9.1; also elsewhere on the board

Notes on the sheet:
Pi and Rasp Power
